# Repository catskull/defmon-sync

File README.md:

# defMon Sync Adapter 
This is an adapter for the Commodore 64 computer. It is used to synchronize a tracker called [defMon](https://www.vandervecken.com/defmon/doku.php?id=download:download) with other music equipment.

It connects to the user port and outputs the following signals:
- LSDJ sync signal.
- nanoloop sync signal.
- midi clock.
- din sync.
- clock signal with adjustable resolution from 24ppqn to 2ppqn for Korg Volcas, TE Pocket Operators, Arturia Microbrute, MI Anushri etc.

It can only work as master.

It should also work with Prophet64.

# Purpose
ScannerBoy originally created and sold these devices but has since stopped. Due to demand, this is an effort to make hardware. To aid in this, the code is being ported to Arduino/MiniCore.

## Building/Flashing
- Install Arduino IDE (1.8.13)
- [Install MiniCore](https://github.com/MCUdude/MiniCore)
- Download/clone this repo and open the defmon-sync.ino file
- Select ATmega8 board from the boards dropdown
- For clock, selecte "External 20 MHz"
- Leave other options the defaults
- Connect a USB-serial adapter to the onboard FTDI header
- Select the serial port in Arduino menu, and hit upload!

# Credits
Original developer: Krzysztof Iwanowski

Additional PCB work by Orgia Mode

Arduino port by catskull

# License
The firmware, PCB layouts and schematics are released under a Creative Commons cc-by-sa 3.0 license.

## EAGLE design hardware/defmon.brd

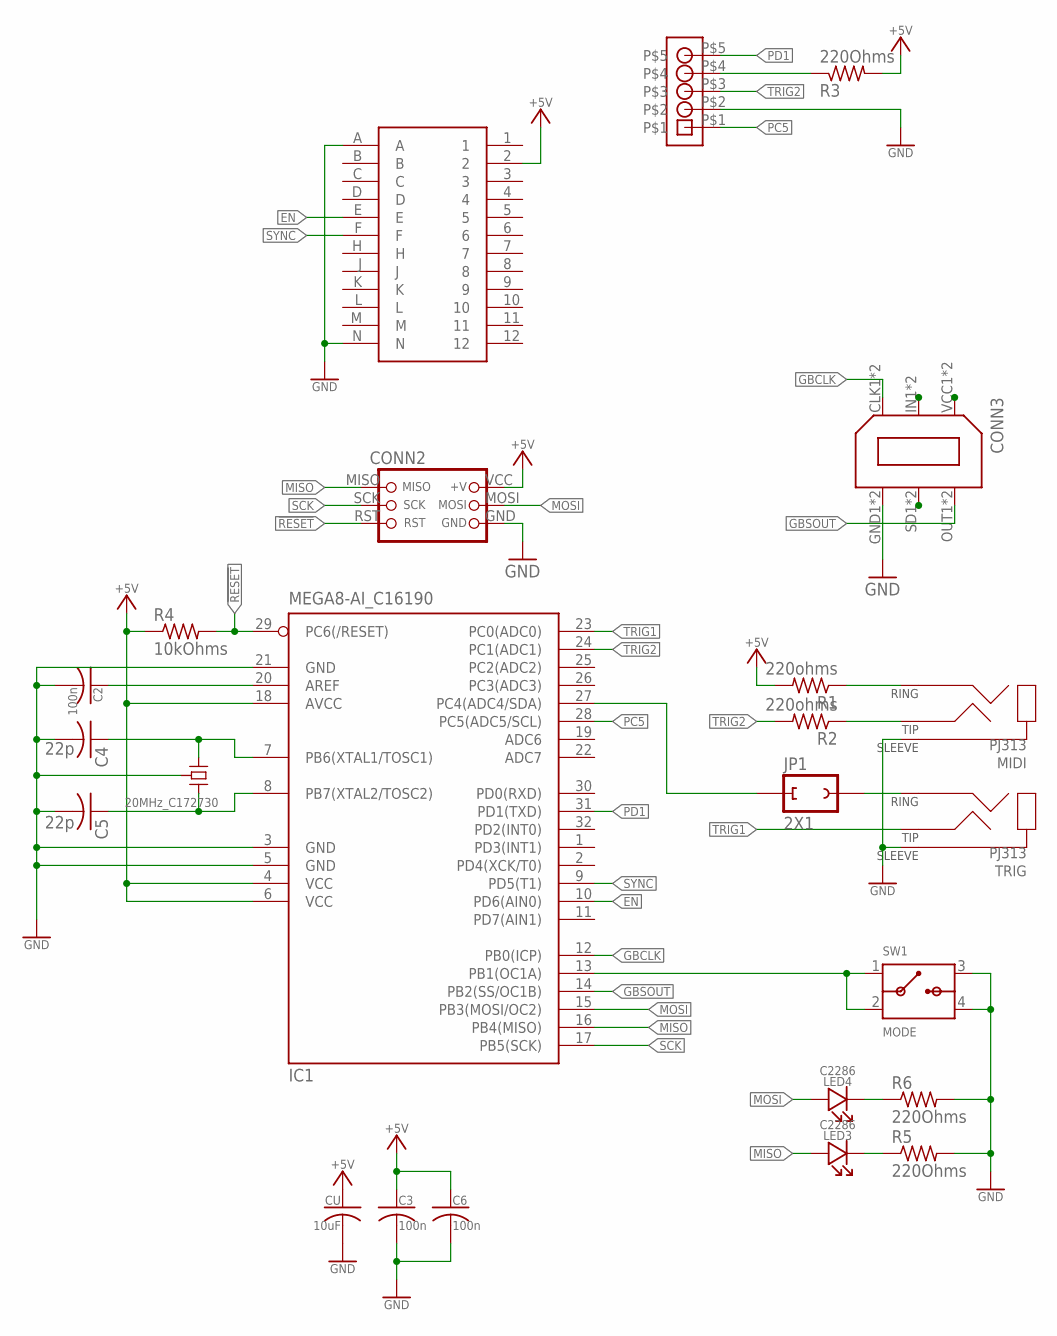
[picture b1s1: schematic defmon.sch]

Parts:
C2, C3, C6: 100n; C0603K
C4, C5: 22p; C0603K
CONN2: DNP; ICSP_SMD_PROBE
CONN3: LINK_PORTFINAL; DUAL_BAORD_LINK_FINAL
CU: 10uF; C0603K
DIN: 1X5
IC1: MEGA8-AI_C16190; TQFP32-08
JP1: 2X1
LED3, LED4: C2286; 0603K
MIDI: PJ313; PJ313D
Q1: 20MHz_C172730; SX3225
R1, R2: 220ohms; R0603
R3, R5, R6: 220Ohms; R0603
R4: 10kOhms; R0603
SW1: MODE; TS5215A
TRIG: PJ313; PJ313D
U$2: CONNECTOR_C64UJ; C64_USERPORT

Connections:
!RESET: CONN2.RST, IC1.29 (PC6(/RESET)), R4.2
+5V: C3.1, C6.1, CONN2.VCC (+V), CU.1, IC1.4 (VCC), IC1.6 (VCC), IC1.18 (AVCC), R1.2, R3.2, R4.1, U$2.2
AREF: C2.1, IC1.20 (AREF)
EN: IC1.10 (PD6(AIN0)), U$2.E
GBCLK: CONN3.CLK1 (CLK), CONN3.CLK2 (CLK), IC1.12 (PB0(ICP))
GBSOUT: CONN3.OUT1 (OUT), CONN3.OUT2 (OUT), IC1.14 (PB2(SS/OC1B))
GND: C2.2, C3.2, C4.2, C5.2, C6.2, CONN2.GND, CONN3.GND1 (GND), CONN3.GND2 (GND), CU.2, DIN.P$2, IC1.3 (GND), IC1.5 (GND), IC1.21 (GND), MIDI.2, MIDI.22 (2), Q1.2 (GND), Q1.4 (GND), R5.2, R6.2, SW1.3 (B1), SW1.4 (B2), TRIG.2, TRIG.22 (2), U$2.A, U$2.N
MISO: CONN2.MISO, IC1.16 (PB4(MISO)), LED3.A
MOSI: CONN2.MOSI, IC1.15 (PB3(MOSI/OC2)), LED4.A
unnamed: CONN3.VCC1 (+5V), CONN3.VCC2 (+5V)
unnamed: CONN3.SD1 (SD), CONN3.SD2 (SD)
unnamed: DIN.P$4, R3.1
unnamed: LED3.C, R5.1
unnamed: CONN3.IN1 (IN), CONN3.IN2 (IN)
unnamed: MIDI.4, MIDI.44 (4), R2.1
unnamed: LED4.C, R6.1
unnamed: C4.1, IC1.7 (PB6(XTAL1/TOSC1)), Q1.3 (X1)
unnamed: JP1.P$2 (2), TRIG.3
unnamed: IC1.27 (PC4(ADC4/SDA)), JP1.P$1 (1)
unnamed: C5.1, IC1.8 (PB7(XTAL2/TOSC2)), Q1.1 (X2)
unnamed: MIDI.3, R1.1
unnamed: IC1.13 (PB1(OC1A)), SW1.1 (A1), SW1.2 (A2)
PC5: DIN.P$1, IC1.28 (PC5(ADC5/SCL))
PD1: DIN.P$5, IC1.31 (PD1(TXD))
SCK: CONN2.SCK, IC1.17 (PB5(SCK))
SYNC: IC1.9 (PD5(T1)), U$2.F
TRIG1: IC1.23 (PC0(ADC0)), TRIG.4, TRIG.44 (4)
TRIG2: DIN.P$3, IC1.24 (PC1(ADC1)), R2.2

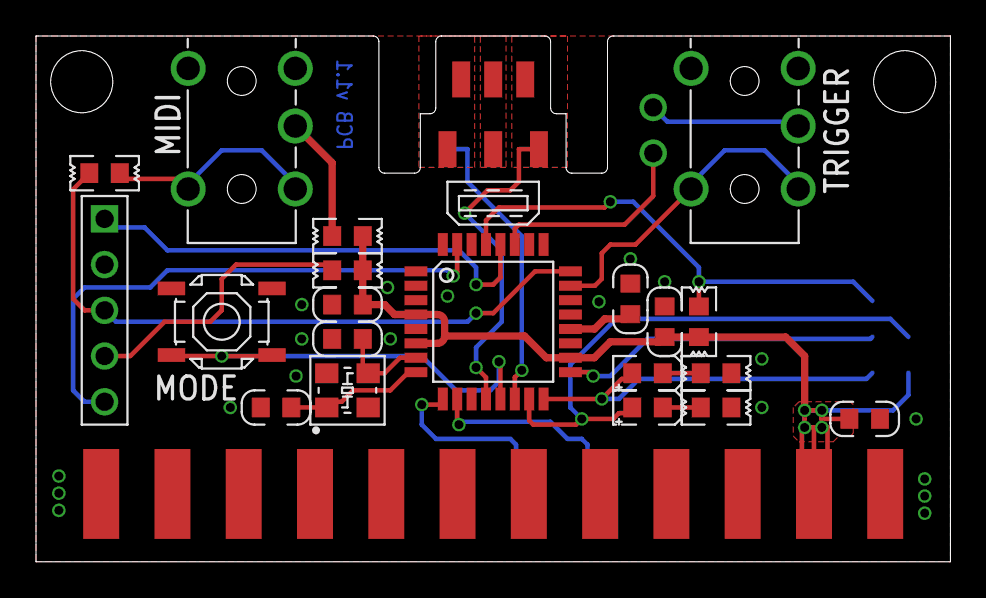
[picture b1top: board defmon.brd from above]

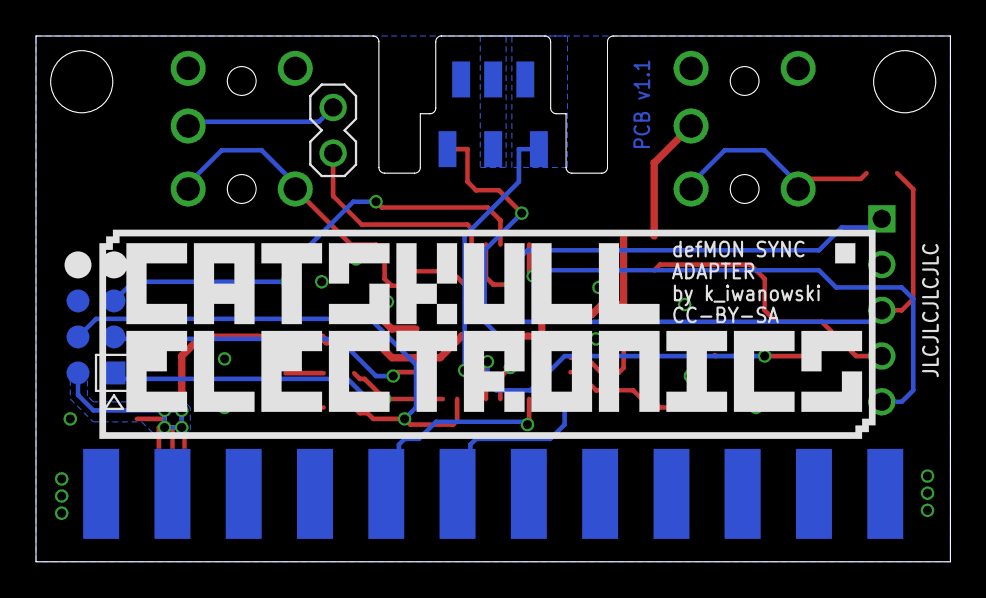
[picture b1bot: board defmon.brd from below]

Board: 2 copper layers, 50.8 x 29.2 mm, 28 parts (4 on the bottom side), 28 nets.

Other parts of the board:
U$1: JLCJLCJLCJLC
U$3, U$8: MOUNT4-40
U$9: CATSKULL_PIXEL_MD

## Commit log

2021-03-29 Make readme markdown and expand it
2021-03-29 Move hardware to a folder
2021-03-29 Initial port of code to Arduino
2021-03-29 Update cad files

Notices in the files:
parts and their libraries:
SparkFun-Aesthetics: Licensing: Creative Commons ShareAlike 4.0 International - https://creativecommons.org/licenses/by-sa/4.0
